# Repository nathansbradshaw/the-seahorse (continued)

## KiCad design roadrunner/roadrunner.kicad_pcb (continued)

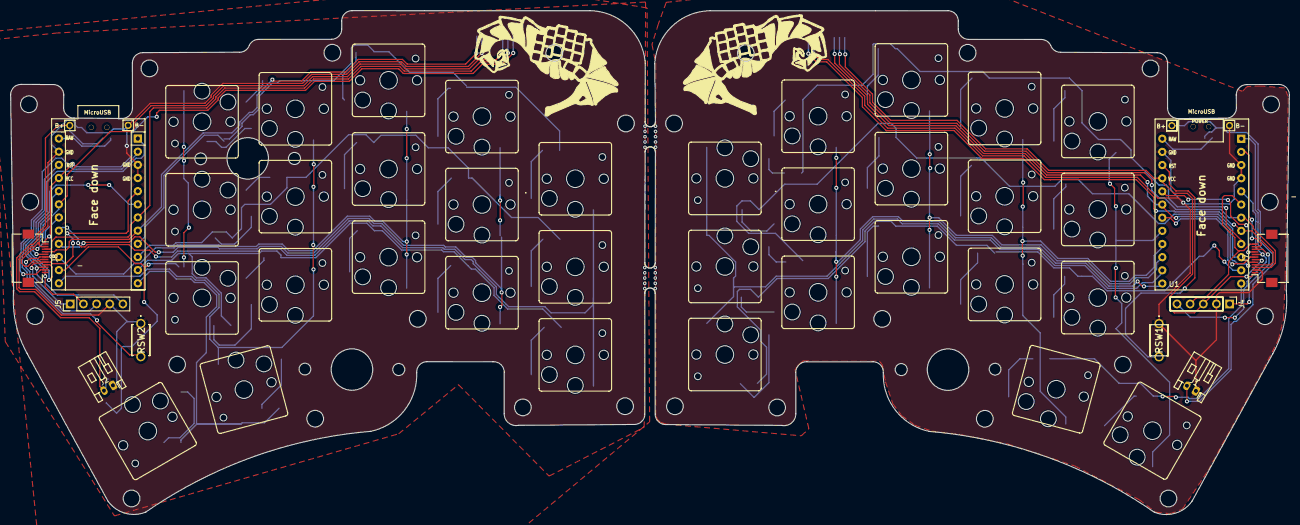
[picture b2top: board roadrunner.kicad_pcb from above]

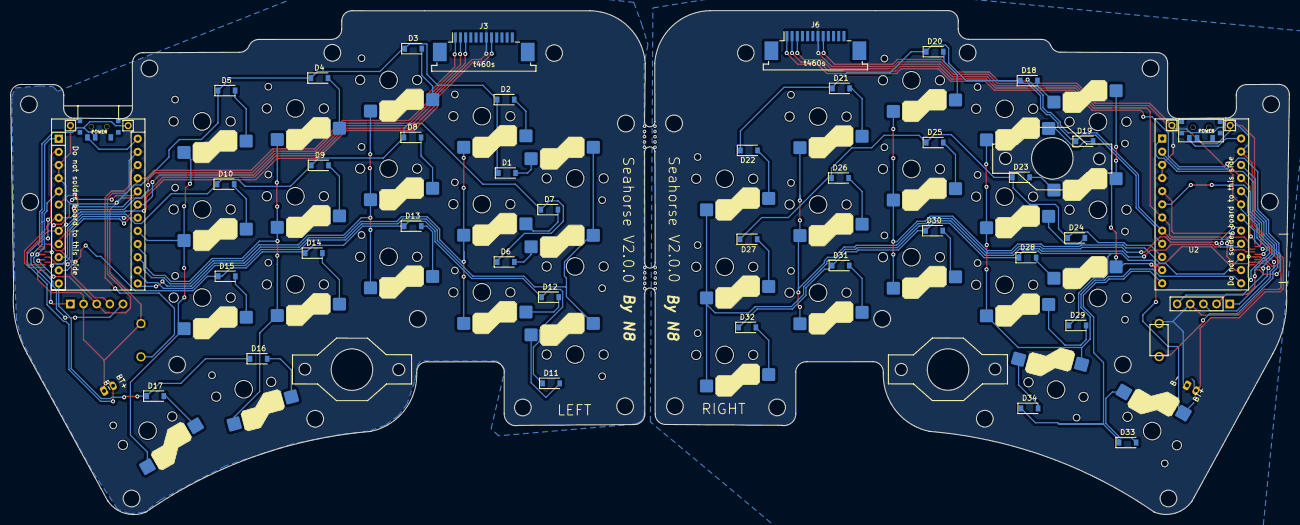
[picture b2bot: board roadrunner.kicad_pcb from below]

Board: 2 copper layers, 246.8 x 97.3 mm, 88 parts (40 on the bottom side), 80 nets.

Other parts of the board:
mouse-bite-2mm-slot1, mouse-bite-2mm-slot1#2: VAL**; mouse-bite-5mm-slot-with-space-for-track

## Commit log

2022-12-04 init
2022-12-04 update schematic
2022-12-05 update shape
2022-12-07 prepare board for order
2023-02-26 add print files
2023-04-06 add svg for wood files
2023-10-15 basic v2 designs
2023-10-15 move button
2023-10-16 begin adding diodes
2023-10-16 place diodes
2023-10-25 begin adding mouse
2024-02-18 feat: add vik
2024-02-19 update thumbpoint layout
2024-02-22 feat: begin routing
2024-02-23 add traces
2024-02-24 feat: finish wiring v2
2024-02-24 chore: specify trackpoint model
2024-03-14 feat: add step file
2024-03-17 feat: make track-point connector reversible
2024-07-04 feat: update readme
2024-07-04 chore: clean up files
2024-07-04 chore: add notable features
2024-07-04 feat: add print files
2024-07-04 chore: update readme
2024-07-04 chore: add print files readme
2024-07-04 chore: add license
2024-07-04 feat: add track point extender stl
2024-07-04 feat: add render
